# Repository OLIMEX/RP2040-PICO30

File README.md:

# RP2040-PICO30

RP2040-PICO30 is Open Source Harrdware re-design of original RP2040-PICO from Rqaspberry Pi 

## Features

* RP2040 CortexM0 microcontroller
* RP2040-PICO pinout and dimentions
* SY8089A 3.3V 2A (3A peak) DCDC power supply
* 30 GPIOs available to the user
* USB-C High Speed USB 2.0 connector for powering the board and communication
* Boot button
* RESET button
* 2MB or 16MB Flash
* Optional UEXT connector (U version)
* Optional status LED (U version)
* Dimensions 51 x 21 mm

Product page: https://www.olimex.com/Products/MicroPython/RP2040-PICO30/open-source-hardware

## Licenses

* Hardware is released under CERN Open Hardware Licence Version 2 - Strongly Reciprocal, all silkscreen credits to Olimex should remain;
* Software is released under GPL3 Licensee
* Documentation is released under CC BY-SA 3.0

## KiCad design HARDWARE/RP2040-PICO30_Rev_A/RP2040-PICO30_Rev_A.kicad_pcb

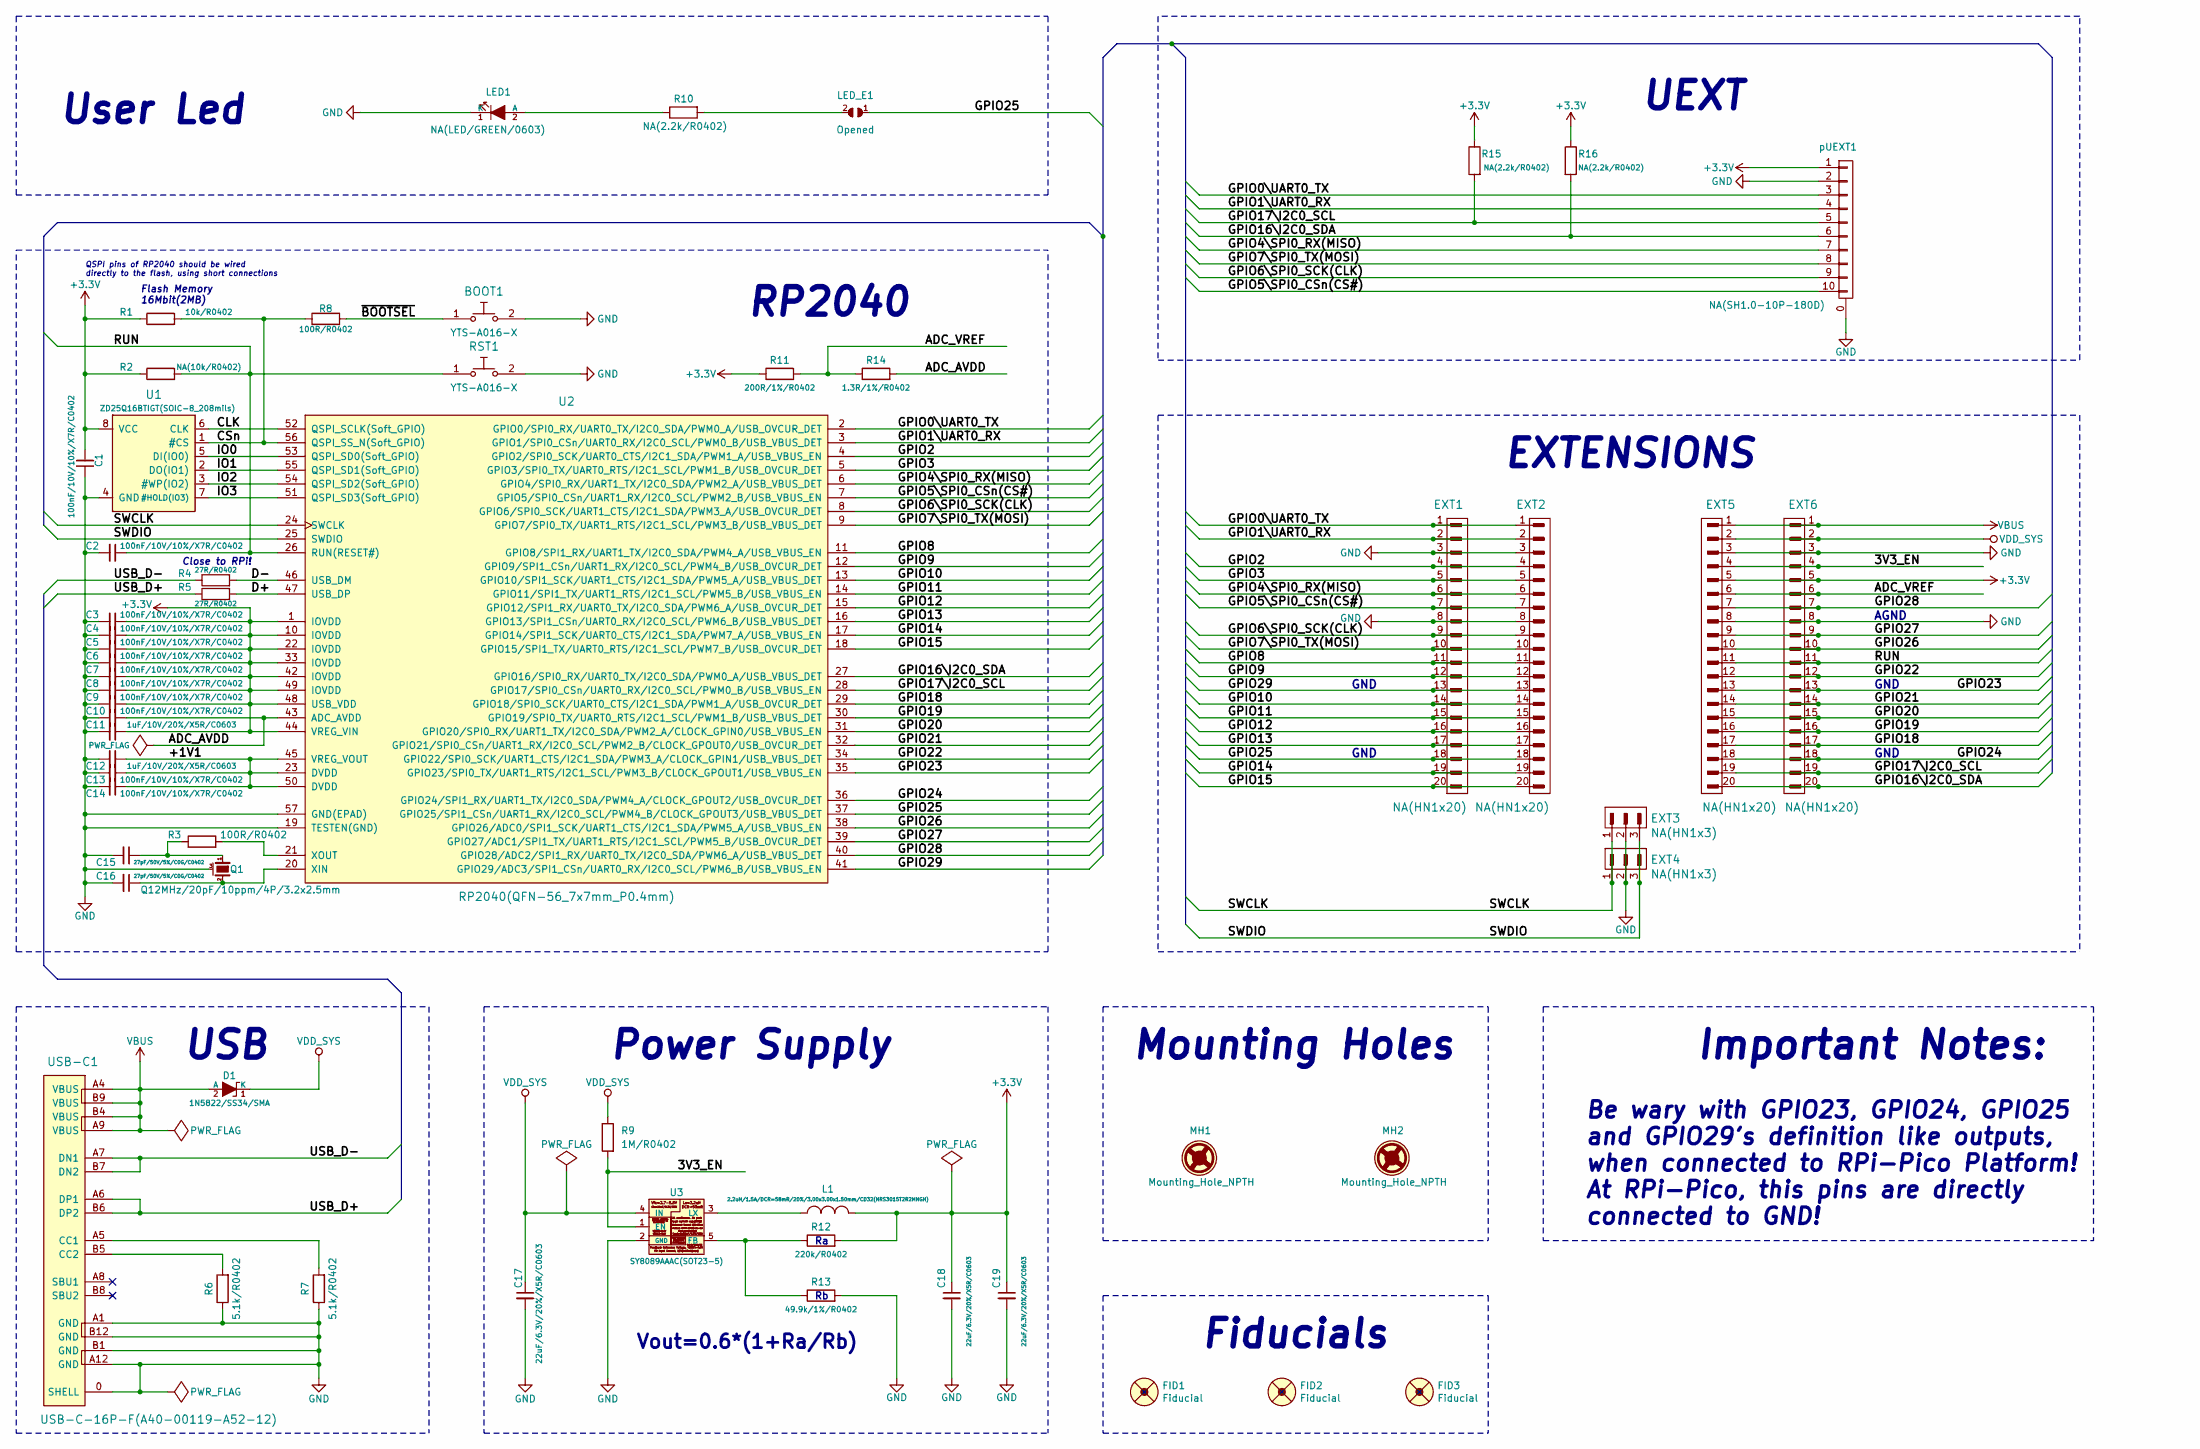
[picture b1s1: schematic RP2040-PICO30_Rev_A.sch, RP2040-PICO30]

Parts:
BOOT1: YTS-A016-X
C1, C2, C3, C4, C5, C6, C7, C8, C9, C10, C13, C14: 100nF/10V/10%/X7R/C0402; C_0402_5MIL_DWS
C11, C12: 1uF/10V/20%/X5R/C0603; C_0603_5MIL_DWS
C15, C16: 27pF/50V/5%/C0G/C0402; C_0402_5MIL_DWS
C17, C18, C19: 22uF/6.3V/20%/X5R/C0603; C_0603_5MIL_DWS
D1: 1N5822/SS34/SMA; SMA-KA
EXT1, EXT2, EXT5, EXT6: NA(HN1x20); HN1x20
EXT3, EXT4: NA(HN1x3); HN1x3
FID1, FID2, FID3: Fiducial; Fiducial1x3
L1: 2.2uH/1.5A/DCR=58mR/20%/3.00x3.00x1.50mm/CD32(NRS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; CD32
LED1: NA(LED/GREEN/0603); LED_0603_KA
LED_E1: Opened; SJ_1_SMALLER
MH1, MH2: Mounting_Hole_NPTH; Mounting_Hole_Drill-2.1mm_Clerance-4mm
Q1: Q12MHz/20pF/10ppm/4P/3.2x2.5mm; TSX-3.2x2.5mm_GND(3)
R1: 10k/R0402; R_0402_5MIL_DWS
R2: NA(10k/R0402); R_0402_5MIL_DWS
R3, R8: 100R/R0402; R_0402_5MIL_DWS
R4, R5: 27R/R0402; R_0402_5MIL_DWS
R6, R7: 5.1k/R0402; R_0402_5MIL_DWS
R9: 1M/R0402; R_0402_5MIL_DWS
R10, R15, R16: NA(2.2k/R0402); R_0402_5MIL_DWS
R11: 200R/1%/R0402; R_0402_5MIL_DWS
R12: 220k/R0402; R_0402_5MIL_DWS
R13: 49.9k/1%/R0402; R_0402_5MIL_DWS
R14: 1.3R/1%/R0402; R_0402_5MIL_DWS
RST1: YTS-A016-X
U1: ZD25Q16BTIGT(SOIC-8_208mils); SO-8_208mil
U2: RP2040(QFN-56_7x7mm_P0.4mm); QFN56_7x7_Pitch_0.4mm
U3: SY8089AAAC(SOT23-5); SOT-23-5
USB-C1: USB-C-16P-F(A40-00119-A52-12); USB2.0_TYPE-C(A40-00119-A52-12)
pUEXT1: NA(SH1.0-10P-180D); BM10B-SRSS-TB

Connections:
+3.3V: C1.2, C3.1, C4.1, C5.1, C6.1, C7.1, C8.1, C9.1, C11.1, C18.1, C19.1, EXT5.5, EXT6.5, L1.2, R1.1, R2.1, R11.1, R12.2, R15.1, R16.1, U1.8 (VCC), U2.1 (IOVDD), U2.10 (IOVDD), U2.22 (IOVDD), U2.33 (IOVDD), U2.42 (IOVDD), U2.44 (VREG_VIN), U2.48 (USB_VDD), U2.49 (IOVDD), pUEXT1.1
/3V3_EN: EXT5.4, EXT6.4, R9.2, U3.1 (EN)
/+1V1: C12.1, C13.1, C14.1, U2.23 (DVDD), U2.45 (VREG_VOUT), U2.50 (DVDD)
/ADC_AVDD: C10.1, R14.2, U2.43 (ADC_AVDD)
/ADC_VREF: EXT5.6, EXT6.6, R11.2, R14.1
/CLK: U1.6 (CLK), U2.52 (QSPI_SCLK(Soft_GPIO))
/CSn: R1.2, R8.1, U1.1 (#CS), U2.56 (QSPI_SS_N(Soft_GPIO))
/D+: R5.2, U2.47 (USB_DP)
/D-: R4.2, U2.46 (USB_DM)
/GPIO0\UART0_TX: EXT1.1, EXT2.1, U2.2 (GPIO0/SPI0_RX/UART0_TX/I2C0_SDA/PWM0_A/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), pUEXT1.3
/GPIO1\UART0_RX: EXT1.2, EXT2.2, U2.3 (GPIO1/SPI0_CSn/UART0_RX/I2C0_SCL/PWM0_B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), pUEXT1.4
/GPIO2: EXT1.4, EXT2.4, U2.4 (GPIO2/SPI0_SCK/UART0_CTS/I2C1_SDA/PWM1_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)
/GPIO3: EXT1.5, EXT2.5, U2.5 (GPIO3/SPI0_TX/UART0_RTS/I2C1_SCL/PWM1_B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)
/GPIO4\SPI0_RX(MISO): EXT1.6, EXT2.6, U2.6 (GPIO4/SPI0_RX/UART1_TX/I2C0_SDA/PWM2_A/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), pUEXT1.7
/GPIO5\SPI0_CSn(CS#): EXT1.7, EXT2.7, U2.7 (GPIO5/SPI0_CSn/UART1_RX/I2C0_SCL/PWM2_B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), pUEXT1.10
/GPIO6\SPI0_SCK(CLK): EXT1.9, EXT2.9, U2.8 (GPIO6/SPI0_SCK/UART1_CTS/I2C1_SDA/PWM3_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), pUEXT1.9
/GPIO7\SPI0_TX(MOSI): EXT1.10, EXT2.10, U2.9 (GPIO7/SPI0_TX/UART1_RTS/I2C1_SCL/PWM3_B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), pUEXT1.8
/GPIO8: EXT1.11, EXT2.11, U2.11 (GPIO8/SPI1_RX/UART1_TX/I2C0_SDA/PWM4_A/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)
/GPIO9: EXT1.12, EXT2.12, U2.12 (GPIO9/SPI1_CSn/UART1_RX/I2C0_SCL/PWM4_B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)
/GPIO10: EXT1.14, EXT2.14, U2.13 (GPIO10/SPI1_SCK/UART1_CTS/I2C1_SDA/PWM5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)
/GPIO11: EXT1.15, EXT2.15, U2.14 (GPIO11/SPI1_TX/UART1_RTS/I2C1_SCL/PWM5_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)
/GPIO12: EXT1.16, EXT2.16, U2.15 (GPIO12/SPI1_RX/UART0_TX/I2C0_SDA/PWM6_A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)
/GPIO13: EXT1.17, EXT2.17, U2.16 (GPIO13/SPI1_CSn/UART0_RX/I2C0_SCL/PWM6_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)
/GPIO14: EXT1.19, EXT2.19, U2.17 (GPIO14/SPI1_SCK/UART0_CTS/I2C1_SDA/PWM7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)
/GPIO15: EXT1.20, EXT2.20, U2.18 (GPIO15/SPI1_TX/UART0_RTS/I2C1_SCL/PWM7_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)
/GPIO16\I2C0_SDA: EXT5.20, EXT6.20, R16.2, U2.27 (GPIO16/SPI0_RX/UART0_TX/I2C0_SDA/PWM0_A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), pUEXT1.6
/GPIO17\I2C0_SCL: EXT5.19, EXT6.19, R15.2, U2.28 (GPIO17/SPI0_CSn/UART0_RX/I2C0_SCL/PWM0_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), pUEXT1.5
/GPIO18: EXT5.17, EXT6.17, U2.29 (GPIO18/SPI0_SCK/UART0_CTS/I2C1_SDA/PWM1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)
/GPIO19: EXT5.16, EXT6.16, U2.30 (GPIO19/SPI0_TX/UART0_RTS/I2C1_SCL/PWM1_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)
/GPIO20: EXT5.15, EXT6.15, U2.31 (GPIO20/SPI0_RX/UART1_TX/I2C0_SDA/PWM2_A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)
/GPIO21: EXT5.14, EXT6.14, U2.32 (GPIO21/SPI0_CSn/UART1_RX/I2C0_SCL/PWM2_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)
/GPIO22: EXT5.12, EXT6.12, U2.34 (GPIO22/SPI0_SCK/UART1_CTS/I2C1_SDA/PWM3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)
/GPIO23: EXT5.13, EXT6.13, U2.35 (GPIO23/SPI0_TX/UART1_RTS/I2C1_SCL/PWM3_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)
/GPIO24: EXT5.18, EXT6.18, U2.36 (GPIO24/SPI1_RX/UART1_TX/I2C0_SDA/PWM4_A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)
/GPIO25: EXT1.18, EXT2.18, LED_E1.1, U2.37 (GPIO25/SPI1_CSn/UART1_RX/I2C0_SCL/PWM4_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)
/GPIO26: EXT5.10, EXT6.10, U2.38 (GPIO26/ADC0/SPI1_SCK/UART1_CTS/I2C1_SDA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)
/GPIO27: EXT5.9, EXT6.9, U2.39 (GPIO27/ADC1/SPI1_TX/UART1_RTS/I2C1_SCL/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)
/GPIO28: EXT5.7, EXT6.7, U2.40 (GPIO28/ADC2/SPI1_RX/UART0_TX/I2C0_SDA/P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)
/GPIO29: EXT1.13, EXT2.13, U2.41 (GPIO29/ADC3/SPI1_CSn/UART0_RX/I2C0_SCL/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)
/IO0: U1.5 (DI(IO0)), U2.53 (QSPI_SD0(Soft_GPIO))
/IO1: U1.2 (DO(IO1)), U2.55 (QSPI_SD1(Soft_GPIO))
/IO2: U1.3 (#WP(IO2)), U2.54 (QSPI_SD2(Soft_GPIO))
/IO3: U1.7 (#HOLD(IO3)), U2.51 (QSPI_SD3(Soft_GPIO))
/RUN: C2.1, EXT5.11, EXT6.11, R2.2, RST1.1, U2.26 (RUN(RESET#))
/SWCLK: EXT3.1, EXT4.1, U2.24 (SWCLK)
/SWDIO: EXT3.3, EXT4.3, U2.25 (SWDIO)
/USB_D+: R5.1, USB-C1.A6 (DP1), USB-C1.B6 (DP2)
/USB_D-: R4.1, USB-C1.A7 (DN1), USB-C1.B7 (DN2)
/~BOOTSEL: BOOT1.1, R8.2
GND: BOOT1.2, C1.1, C2.2, C3.2, C4.2, C5.2, C6.2, C7.2, C8.2, C9.2, C10.2, C11.2, C12.2, C13.2, C14.2, C15.2, C16.2, C17.2, C18.2, C19.2, EXT1.3, EXT1.8, EXT2.3, EXT2.8, EXT3.2, EXT4.2, EXT5.3, EXT5.8, EXT6.3, EXT6.8, LED1.1 (K), Q1.3 (case), R6.1, R7.1, R13.2, RST1.2, U1.4 (GND), U2.19 (TESTEN(GND)), U2.57 (GND(EPAD)), U3.2 (GND), USB-C1.0 (SHELL), USB-C1.A1 (GND), USB-C1.A12 (GND), USB-C1.B1 (GND), USB-C1.B12 (GND), pUEXT1.0, pUEXT1.2
unnamed: C15.1, Q1.1, R3.1
unnamed: C16.1, Q1.2, U2.20 (XIN)
unnamed: L1.1, U3.3 (LX)
unnamed: LED1.2 (A), R10.1
unnamed: LED_E1.2, R10.2
unnamed: R3.2, U2.21 (XOUT)
unnamed: R6.2, USB-C1.B5 (CC2)
unnamed: R7.2, USB-C1.A5 (CC1)
unnamed: R12.1, R13.1, U3.5 (FB)
VBUS: D1.2 (A), EXT5.1, EXT6.1, USB-C1.A4 (VBUS), USB-C1.A9 (VBUS), USB-C1.B4 (VBUS), USB-C1.B9 (VBUS)
VDD_SYS: C17.1, D1.1 (K), EXT5.2, EXT6.2, R9.1, U3.4 (IN)

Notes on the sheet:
Fiducials
Mounting Holes
Power Supply
Vout=0.6*(1+Ra/Rb)
UEXT
Flash Memory 16Mbit(2MB)
Close to RPi!
QSPI pins of RP2040 should be wired directly to the flash, using short connections
EXTENSIONS
USB
User Led
RP2040
AGND
GND
Important Notes:
Be wary with GPIO23, GPIO24, GPIO25 and GPIO29's definition like outputs, when connected to RPi-Pico Platform! At RPi-Pico, this pins are directly connected to GND!

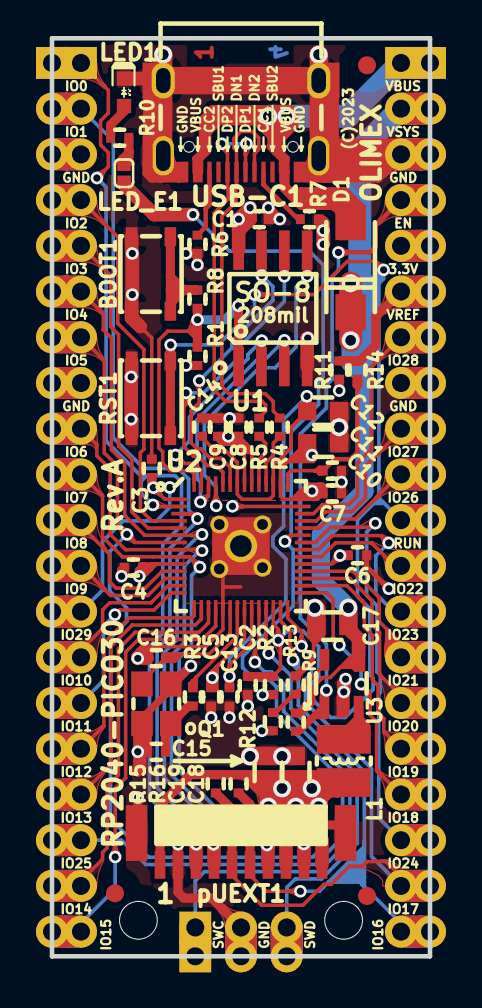
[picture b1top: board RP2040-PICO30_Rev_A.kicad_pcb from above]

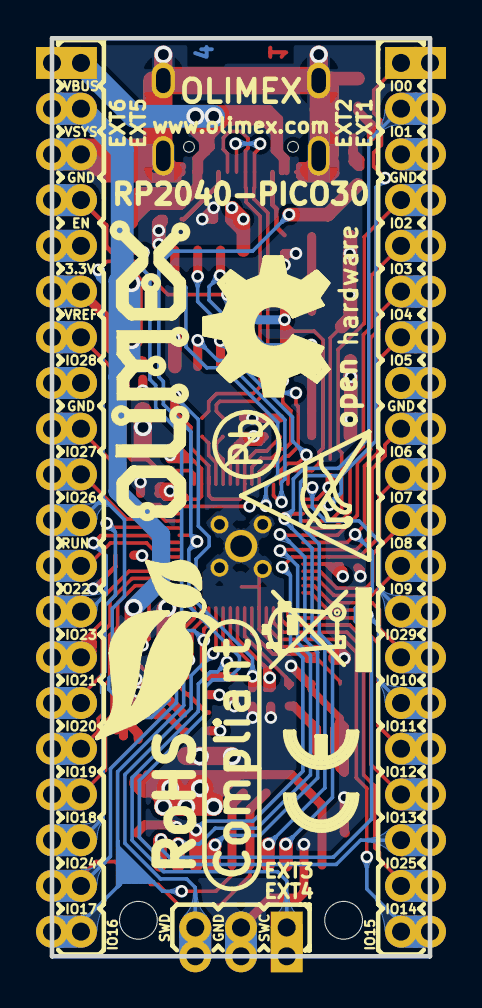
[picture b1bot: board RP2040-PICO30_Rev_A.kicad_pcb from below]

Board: 4 copper layers, 21.0 x 51.0 mm, 65 parts (13 on the bottom side), 61 nets.

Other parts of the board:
Logo_OLIMEX_TB-Bottom: Logo_OLIMEX_TB
Sign_Antistatic: Sign_Antistatic
Sign_CE: CE_Sign
Sign_OSHW_8x8: Sign_OSHW_8x8
Sign_PB-Free: Sign_PB-Free
Sign_RecycleBin: Sign_RecycleBin; Sign_RecycleBin_1
Sign_RoHS: Sign_RoHS; Sign_RoHS_1

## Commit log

2023-05-26 initial update
2023-06-27 Update
    Remove backups
2023-06-27 Update
    Improved design files
2023-06-27 Update
    Manual update

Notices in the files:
HARDWARE/RP2040-PICO30_Rev_A/RP2040-PICO30_Rev_A.kicad_pcb:
(C)2023
